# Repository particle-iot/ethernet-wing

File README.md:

# ethernet-wing
*Hardware design files for the Particle Ethernet Wing*

The Ethernet FeatherWing is the fastest way to add wired connectivity to your Argon, Boron, or Xenon and turns any Particle Mesh developer kit into an Ethernet gateway. Based on the WIZnet W5500 chip, this side-by-side FeatherWing maintains great RF performance even while adding Ethernet connectivity to any Particle Mesh device.

The form-factor is based around the Adafruit FeatherWing Tripler. The two side connectors allow you to plug in one Particle Mesh device along with a Feather accessory.

- 10BaseT/100BaseTX Ethernet 
- Support Auto Negotiation (Full and half duplex, for both 10BaseT and 100BaseTX)

## Pin Map

|Mesh Pin|Ethernet FeatherWing Pin   |
|:-------|:--------------------------|
|MISO    | SPI MISO                  |
|MOSI    | SPI MOSI                  |
|SCK     | SPI SCK                   |
|D3      | nRESET<sup>[1]</sup>      |
|D4      | nINTERRUPT<sup>[1]</sup>  |
|D5      | nCHIP SELECT<sup>[1]</sup>|

**Notes:**

<sup>[1]</sup> These pins are connected via jumper pads on the bottom. You can cut these jumper traces and rewire them to a different pin on the Mesh device if the need arises. However the Device OS does not allow use of other pins (as of 0.8.0-rc.27).

The Ethernet driver for this wing is baked into the Mesh Device OS. When you set up a new Particle Mesh device that is plugged into an Ethernet FeatherWing, simply select the _USE WITH ETHERNET?_ option on your Particle mobile app and it should recognize and talk over Ethernet automagically. It's that simple.

## PoE (Power over Ethernet)

The PoE (Power over Ethernet) adapter for the Ethernet FeatherWing plugs into the Ethernet side of the FeatherWing. 

It uses the Silvertel Ag9905M and can supply 1800 mA to your device and any Feather accessories. It is a Class 0 IEEE 802.3af device.

| Parameter | Minimum | Typical | Maximum | Units |
| --- | --- | --- | --- | --- |
| Input Supply Voltage | 36 | 48 | 57 | Volts |
| Operating Temperature<sup>1</sup> | -40 | 25 | 70 | &deg;C |
| Output Voltage | | 5 | | V |
| Output Current | | | 1800 | mA |

<sup>1</sup>Operating temperature of the Ag9905M module only. The operating temperature range of the Xenon is smaller, -20 to +60&deg;C.

Note that because the Ethernet FeatherWing with PoE supplies 5V to the device by the VUSB pin, you should not power it by both PoE and the USB serial port at the same time.

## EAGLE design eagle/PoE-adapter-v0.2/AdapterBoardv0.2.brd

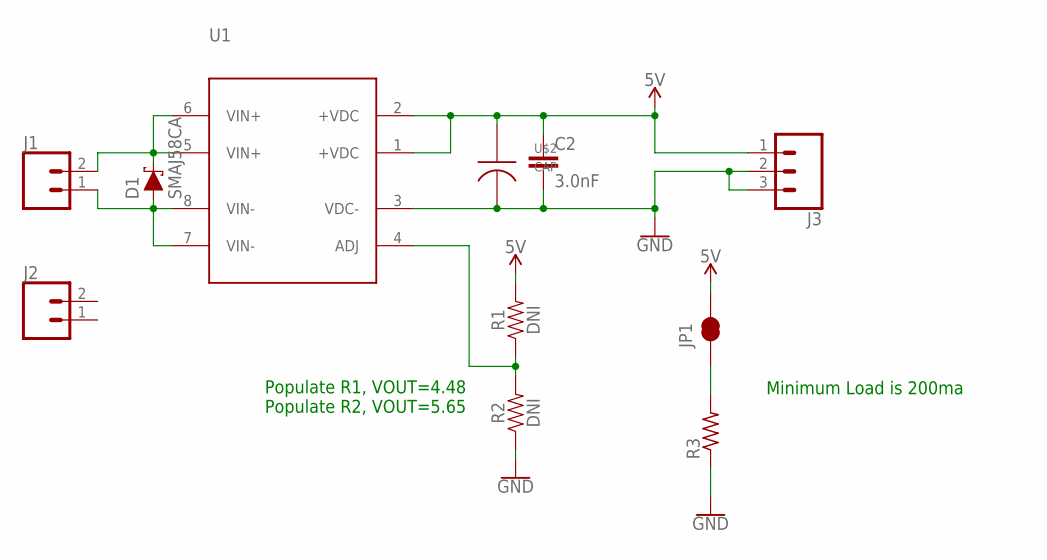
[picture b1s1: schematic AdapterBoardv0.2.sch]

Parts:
C2: 3.0nF; 0603
D1: SMAJ58CA; SMA-DIODE
J1, J2: CONN_02; 1X02
J3: CONN_03; 1X03
JP1: JUMPER-SMT_2_NC_TRACE_NO-SILK; SMT-JUMPER_2_NC_TRACE_NO-SILK
R1, R2: DNI; 0603
R3: R-US_R1210; R1210
U1: PARTICLE_AG9800AG99; AG9900
U$2: CAP

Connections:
5V: C2.1, J3.1, JP1.2, R1.2, U1.1 (+VDC), U1.2 (+VDC), U$2.A
ADJ: R1.1, R2.2, U1.4 (ADJ)
GND: C2.2, J3.2, J3.3, R2.1, R3.1, U1.3 (VDC-), U$2.C
unnamed: JP1.1, R3.2
V+: D1.C, J1.2, U1.5 (VIN+), U1.6 (VIN+)
V-: D1.A, J1.1, U1.7 (VIN-), U1.8 (VIN-)

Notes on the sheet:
Populate R1, VOUT=4.48 Populate R2, VOUT=5.65
Minimum Load is 200ma

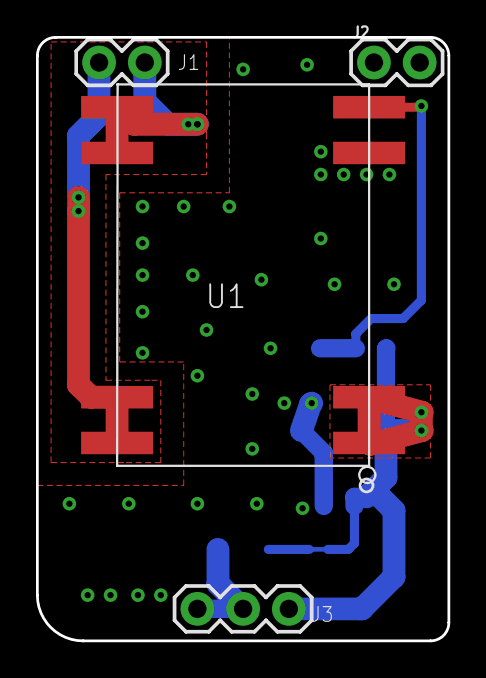
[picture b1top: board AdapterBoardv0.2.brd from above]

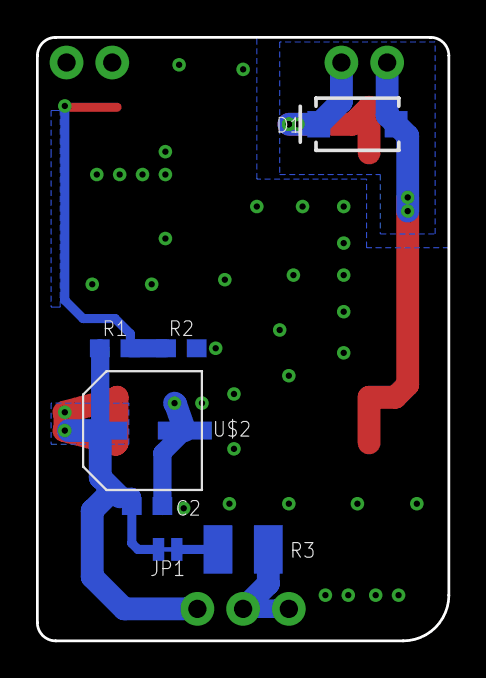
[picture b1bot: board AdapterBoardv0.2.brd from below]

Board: 2 copper layers, 22.9 x 33.5 mm, 11 parts (7 on the bottom side), 6 nets.

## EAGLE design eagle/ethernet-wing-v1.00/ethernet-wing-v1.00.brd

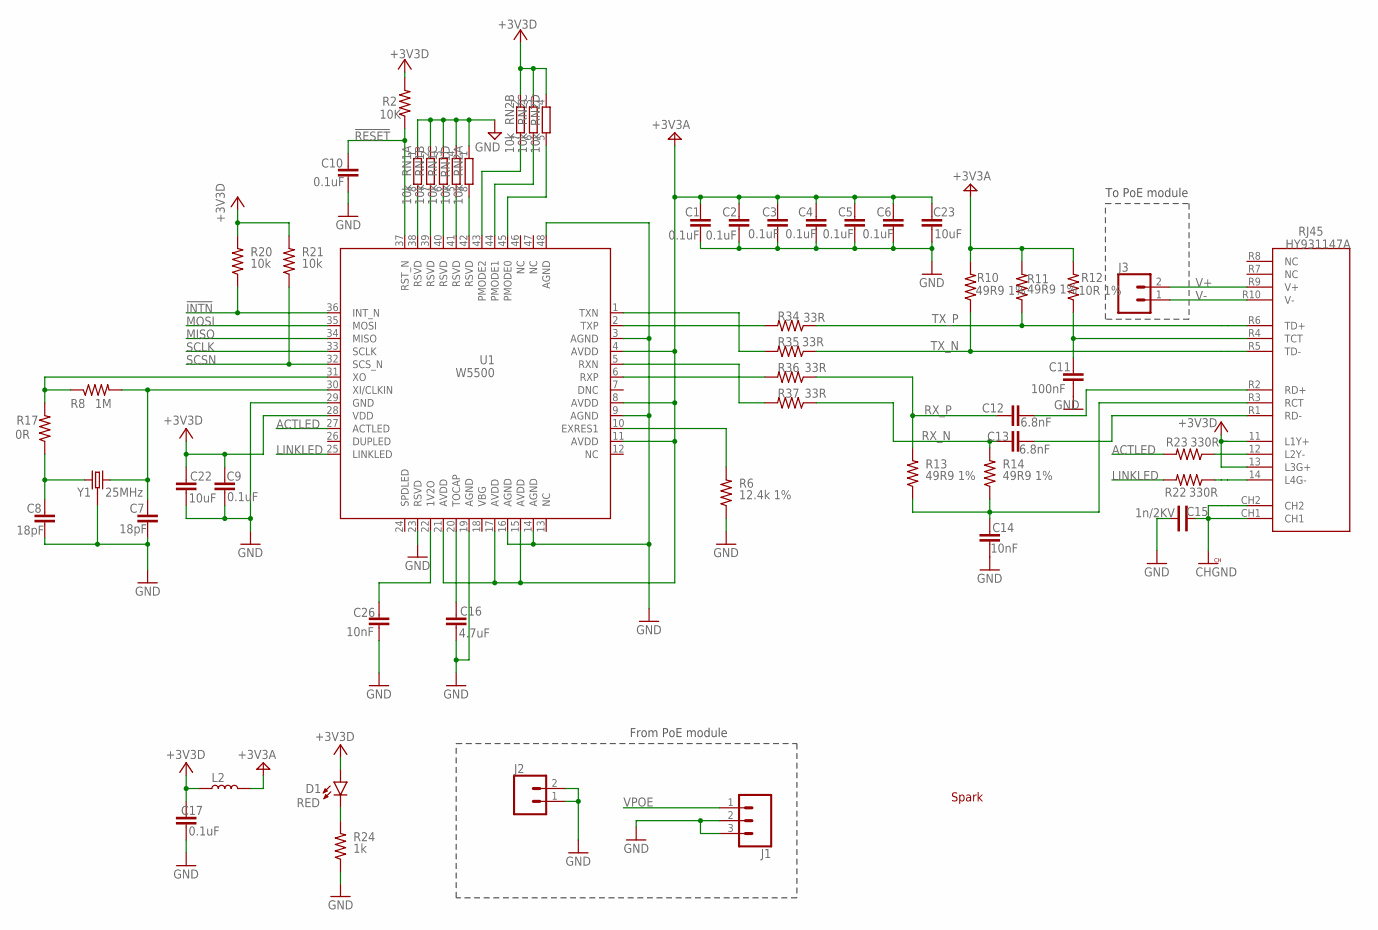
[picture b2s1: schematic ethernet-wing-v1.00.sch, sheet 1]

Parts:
C1, C2, C3, C4, C5, C6, C9, C10, C17: 0.1uF; C0402_B
C7, C8: 18pF; C0402_B
C11: 100nF; C0402_B
C12, C13: 6.8nF; C0402_B
C14, C26: 10nF; C0402_B
C15: 1n/2KV; C-1808
C16: 4.7uF; 0603
C22, C23: 10uF; 0603
D1: RED; LED-0603
J1: CONN_03; 1X03
J2, J3: CONN_02; 1X02
L2: INDUCTOR-0805-3.3UH; 0805
R2: 10K; R0402_B
R6: 12.4k 1%; R0402_B
R8: 1M; R0402_B
R10, R11, R13, R14: 49R9 1%; R0402_B
R12: 10R 1%; R0402_B
R17: 0R; R0402_B
R20, R21: 10k; R0402_B
R22, R23: 330R; R0402_B
R24: 1k; R0402_B
R34, R35, R36, R37: 33R; R0402_B
RJ45: HY931147A; ARDUINO-ETHERNET-SHIELD2-V2_CONNETTORI_POE-RJ45
RN1, RN2: 10k; 4X0402ARV341
U1: W5500
U$2: SPARK_LOGO2
Y1: 25MHz; CRYSTAL-SMD-3.2X2.5MM

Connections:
!INTN: R20.1, U1.36 (INT_N); also elsewhere on the board
!RESET: C10.2, R2.1, U1.37 (RST_N); also elsewhere on the board
+3V3: C9.2, C17.2, C22.1, D1.A, L2.1, R2.2, R20.2, R21.2, RJ45.11 (L1Y+), RJ45.13 (L3G+), RN2.2 (1), RN2.3 (1), RN2.4 (1), U1.28 (VDD); also elsewhere on the board
+3V3A: C1.2, C2.2, C3.2, C4.2, C5.2, C6.2, C23.1, L2.2, R10.2, R11.2, R12.2, U1.4 (AVDD), U1.8 (AVDD), U1.11 (AVDD), U1.15 (AVDD), U1.17 (AVDD), U1.21 (AVDD)
ACTLED: R23.2, U1.27 (ACTLED)
CHGND: C15.P$1, RJ45.CH1, RJ45.CH2
GND: C1.1, C2.1, C3.1, C4.1, C5.1, C6.1, C7.1, C8.1, C9.1, C10.1, C11.1, C14.1, C15.P$2, C16.2, C17.1, C22.2, C23.2, C26.1, J1.2, J1.3, J2.1, J2.2, R6.1, R24.1, RN1.1, RN1.2 (1), RN1.3 (1), RN1.4 (1), RN2.1, U1.3 (AGND), U1.9 (AGND), U1.14 (AGND), U1.16 (AGND), U1.19 (AGND), U1.23 (RSVD), U1.29 (GND), U1.48 (AGND), Y1.2 (3), Y1.4 (3); also elsewhere on the board
LINKLED: R22.2, U1.25 (LINKLED)
MISO: U1.34 (MISO); also elsewhere on the board
MOSI: U1.35 (MOSI); also elsewhere on the board
unnamed: RN2.7 (2), U1.43 (PMODE2)
unnamed: RN2.6 (2), U1.44 (PMODE1)
unnamed: RN2.5 (2), U1.45 (PMODE0)
unnamed: RN1.8 (2), U1.38 (RSVD)
unnamed: RN1.7 (2), U1.39 (RSVD)
unnamed: RN1.6 (2), U1.40 (RSVD)
unnamed: RN1.5 (2), U1.41 (RSVD)
unnamed: RN2.8 (2), U1.42 (RSVD)
unnamed: C8.2, R17.1, Y1.1
unnamed: C16.1, U1.20 (TOCAP)
unnamed: C26.2, U1.22 (1V2O)
unnamed: R6.2, U1.10 (EXRES1)
unnamed: C14.2, R13.1, R14.1, RJ45.R3 (RCT)
unnamed: D1.C, R24.2
unnamed: C11.2, R12.1, RJ45.R4 (TCT)
unnamed: R8.1, R17.2, U1.31 (XO)
unnamed: C7.2, R8.2, U1.30 (XI/CLKIN), Y1.3 (2)
unnamed: R23.1, RJ45.12 (L2Y-)
unnamed: R22.1, RJ45.14 (L4G-)
RR_N: C13.2, RJ45.R1 (RD-)
RR_P: C12.2, RJ45.R2 (RD+)
RX_N: C13.1, R14.2, R37.1
RX_P: C12.1, R13.2, R36.1
R_N: R37.2, U1.5 (RXN)
R_P: R36.2, U1.6 (RXP)
SCLK: U1.33 (SCLK); also elsewhere on the board
SCSN: R21.1, U1.32 (SCS_N); also elsewhere on the board
TX_N: R10.1, R35.1, RJ45.R5 (TD-)
TX_P: R11.1, R34.1, RJ45.R6 (TD+)
T_N: R35.2, U1.1 (TXN)
T_P: R34.2, U1.2 (TXP)
V+: J3.2, RJ45.R9 (V+)
V-: J3.1, RJ45.R10 (V-)
VPOE: J1.1; also elsewhere on the board

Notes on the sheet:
To PoE module
From PoE module

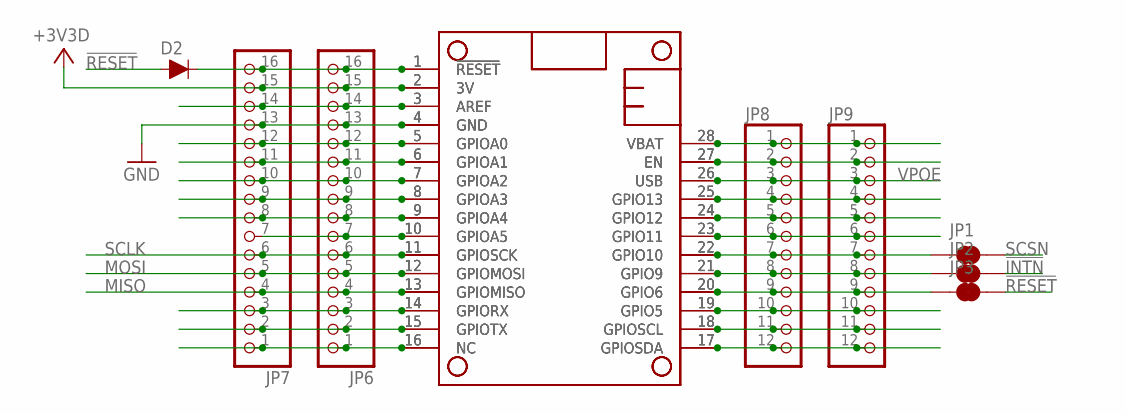
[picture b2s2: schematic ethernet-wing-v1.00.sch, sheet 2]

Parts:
D2: DIODE-BAS16J; SOD-323
JP1, JP2, JP3: JUMPER-SMT_2_NC_TRACE_NO-SILK; SMT-JUMPER_2_NC_TRACE_NO-SILK
JP6, JP7: MICROBUILDER_HEADER-1X16_76MIL; MICROBUILDER_1X16_ROUND_76MIL
JP8, JP9: MICROBUILDER_HEADER-1X1276MIL; MICROBUILDER_1X12_ROUND_76MIL
MS1, MS2: MICROBUILDER_FEATHERWING_NODIM; MICROBUILDER_FEATHERWING_DIM

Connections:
!INTN: JP2.2; also elsewhere on the board
!RESET: D2.A, JP3.2; also elsewhere on the board
!RESET!!: D2.C, JP6.16, JP7.16, MS1.1 (!RESET), MS2.1 (!RESET)
+3V3: JP6.15, JP7.15, MS1.2 (3V), MS2.2 (3V); also elsewhere on the board
GND: JP6.13, JP7.13, MS1.4 (GND), MS2.4 (GND); also elsewhere on the board
MISO: JP6.4, JP7.4, MS1.13 (GPIOMISO), MS2.13 (GPIOMISO); also elsewhere on the board
MOSI: JP6.5, JP7.5, MS1.12 (GPIOMOSI), MS2.12 (GPIOMOSI); also elsewhere on the board
unnamed: JP6.14, JP7.14, MS1.3 (AREF), MS2.3 (AREF)
unnamed: JP8.2, JP9.2, MS1.27 (EN), MS2.27 (EN)
unnamed: JP8.10, JP9.10, MS1.19 (GPIO5), MS2.19 (GPIO5)
unnamed: JP3.1, JP8.9, JP9.9, MS1.20 (GPIO6), MS2.20 (GPIO6)
unnamed: JP2.1, JP8.8, JP9.8, MS1.21 (GPIO9), MS2.21 (GPIO9)
unnamed: JP1.1, JP8.7, JP9.7, MS1.22 (GPIO10), MS2.22 (GPIO10)
unnamed: JP8.6, JP9.6, MS1.23 (GPIO11), MS2.23 (GPIO11)
unnamed: JP8.5, JP9.5, MS1.24 (GPIO12), MS2.24 (GPIO12)
unnamed: JP8.4, JP9.4, MS1.25 (GPIO13), MS2.25 (GPIO13)
unnamed: JP6.12, JP7.12, MS1.5 (GPIOA0), MS2.5 (GPIOA0)
unnamed: JP6.11, JP7.11, MS1.6 (GPIOA1), MS2.6 (GPIOA1)
unnamed: JP6.10, JP7.10, MS1.7 (GPIOA2), MS2.7 (GPIOA2)
unnamed: JP6.9, JP7.9, MS1.8 (GPIOA3), MS2.8 (GPIOA3)
unnamed: JP6.8, JP7.8, MS1.9 (GPIOA4), MS2.9 (GPIOA4)
unnamed: JP6.7, JP7.7, MS1.10 (GPIOA5), MS2.10 (GPIOA5)
unnamed: JP6.3, JP7.3, MS1.14 (GPIORX), MS2.14 (GPIORX)
unnamed: JP8.11, JP9.11, MS1.18 (GPIOSCL), MS2.18 (GPIOSCL)
unnamed: JP8.12, JP9.12, MS1.17 (GPIOSDA), MS2.17 (GPIOSDA)
unnamed: JP6.2, JP7.2, MS1.15 (GPIOTX), MS2.15 (GPIOTX)
unnamed: JP6.1, JP7.1, MS1.16 (NC), MS2.16 (NC)
SCLK: JP6.6, JP7.6, MS1.11 (GPIOSCK), MS2.11 (GPIOSCK); also elsewhere on the board
SCSN: JP1.2; also elsewhere on the board
VBAT: JP8.1, JP9.1, MS1.28 (VBAT), MS2.28 (VBAT)
VPOE: JP8.3, JP9.3, MS1.26 (USB), MS2.26 (USB); also elsewhere on the board

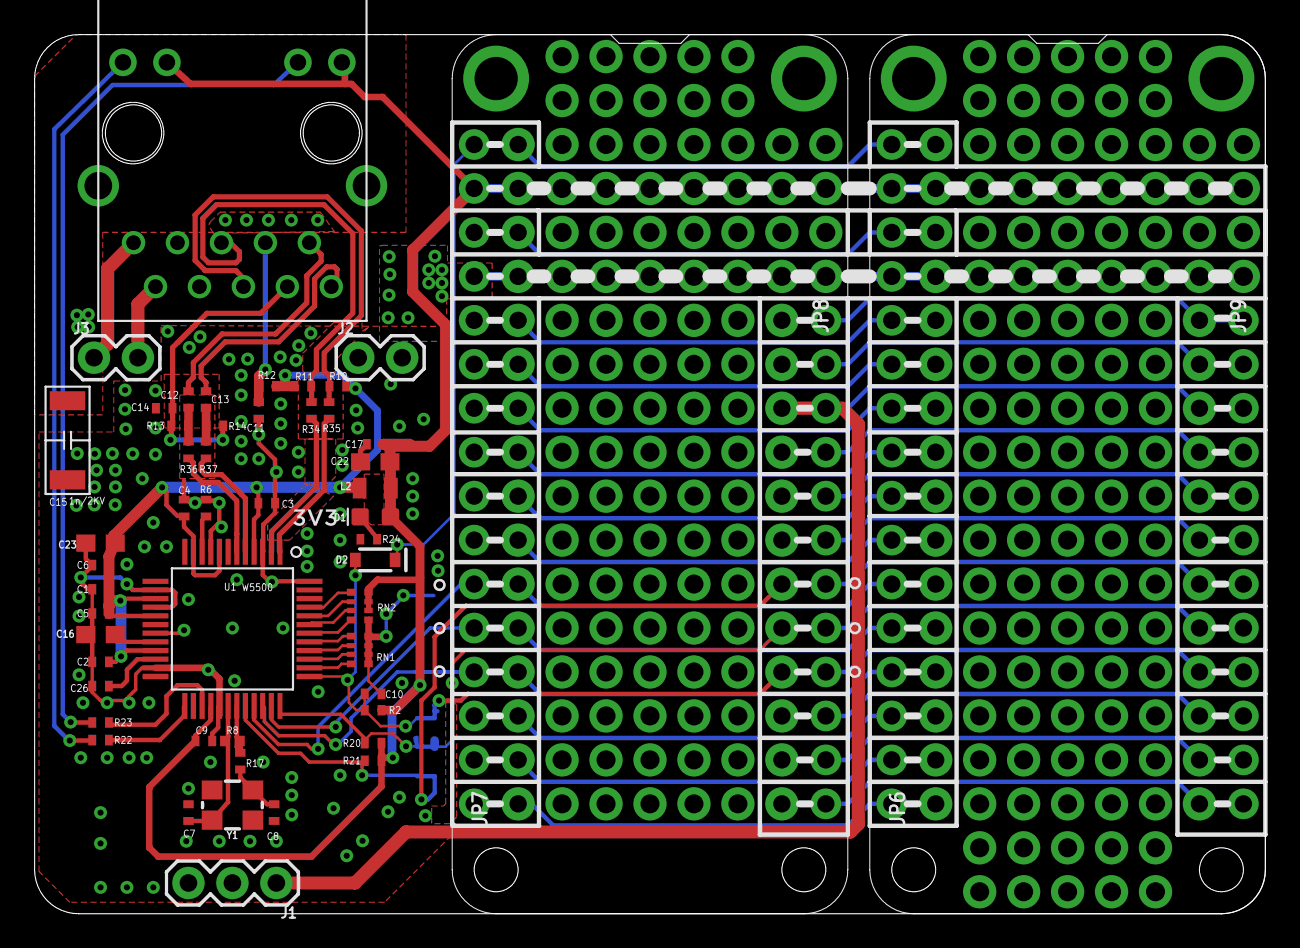
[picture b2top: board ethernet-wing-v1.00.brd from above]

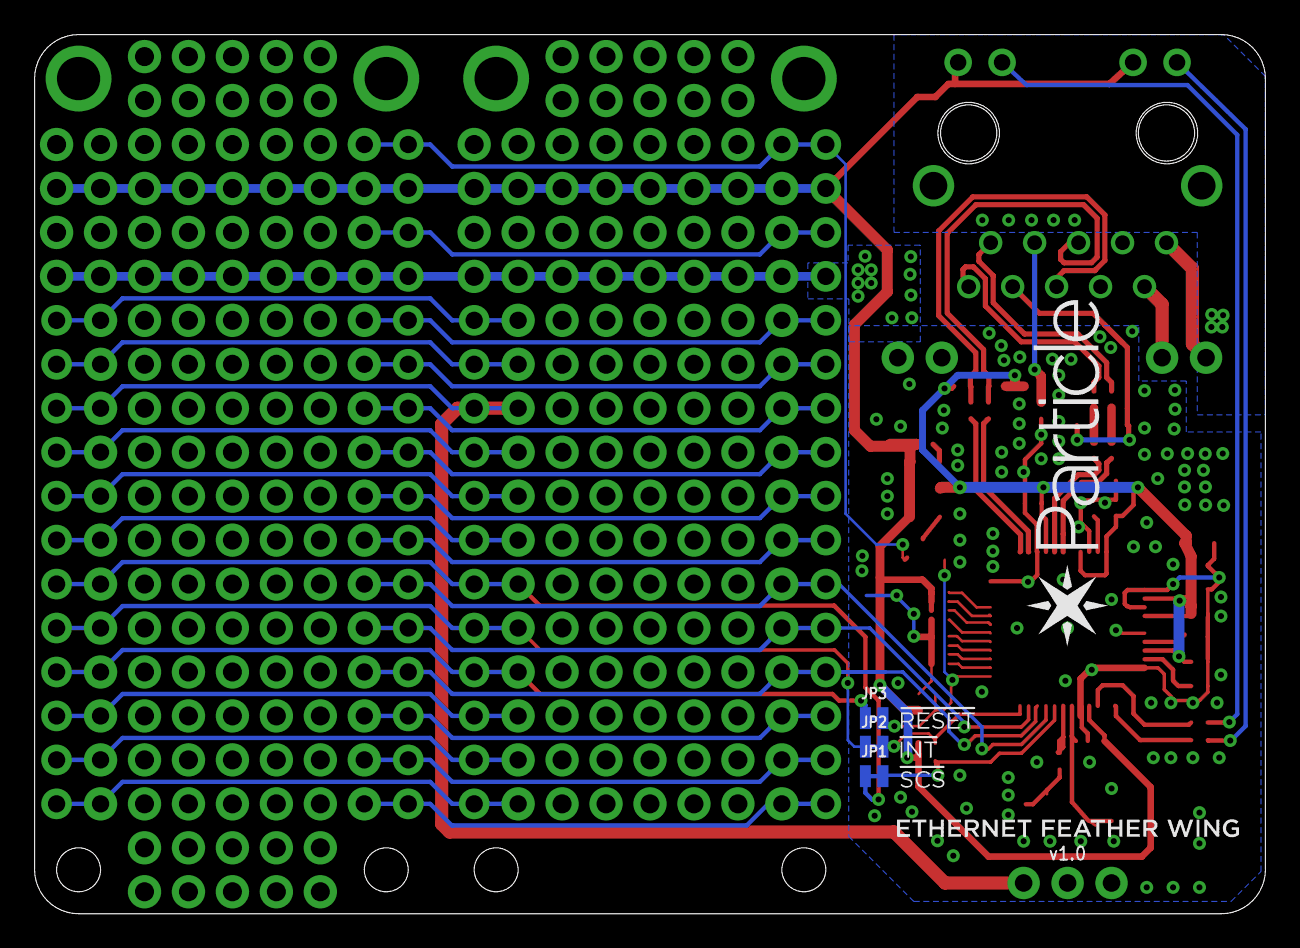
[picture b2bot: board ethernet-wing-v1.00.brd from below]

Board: 2 copper layers, 71.1 x 50.8 mm, 59 parts (3 on the bottom side), 66 nets.

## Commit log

2018-10-22 added board design files
2019-01-28 Add PoE adapter
2020-07-20 Added license

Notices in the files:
parts and their libraries:
SparkFun-Capacitors: Licensing: Creative Commons ShareAlike 4.0 International - https://creativecommons.org/licenses/by-sa/4.0
